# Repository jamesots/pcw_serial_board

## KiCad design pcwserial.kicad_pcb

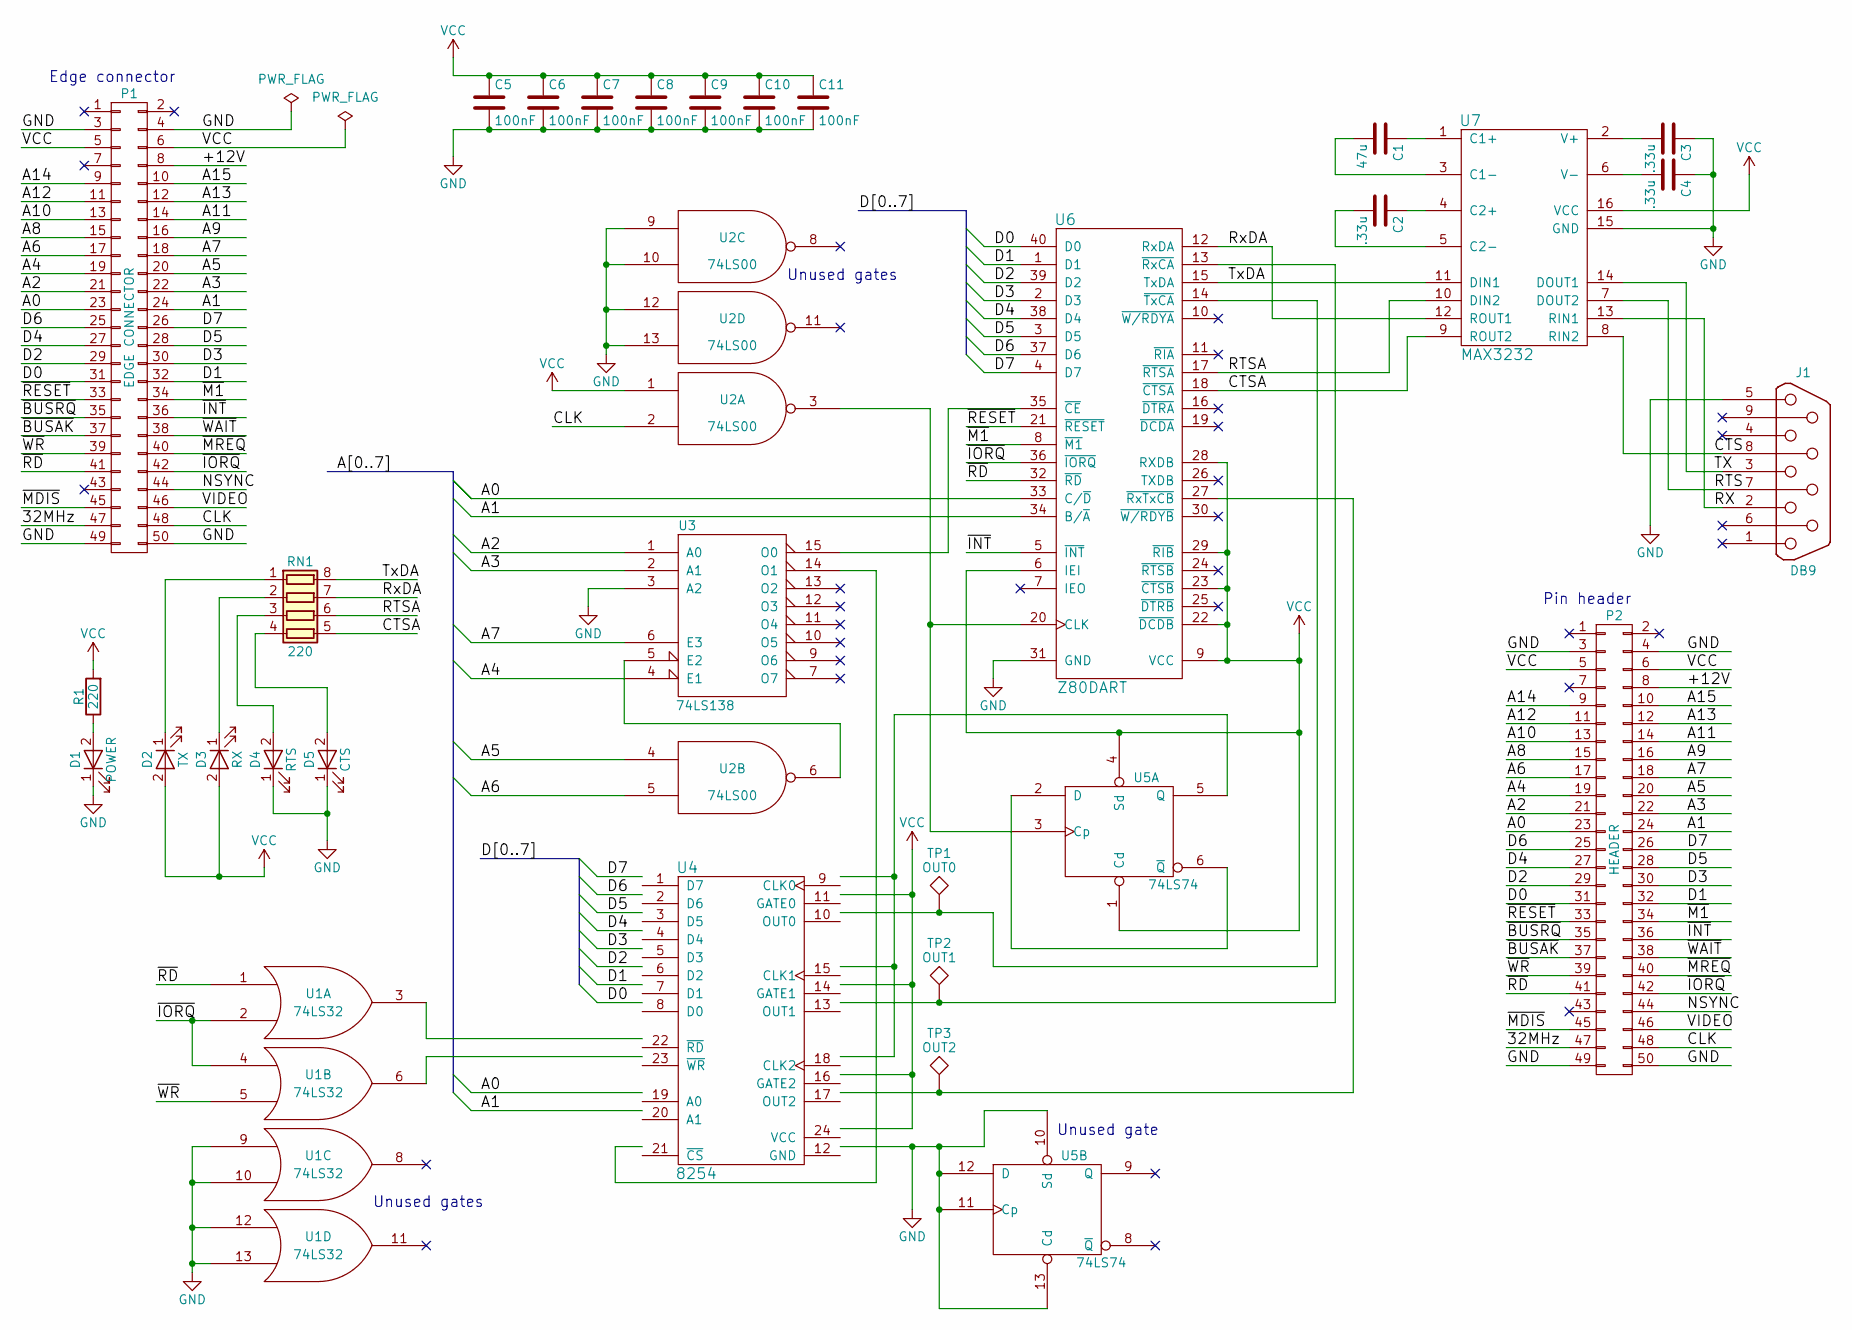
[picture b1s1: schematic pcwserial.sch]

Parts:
C1: 47u; C_Disc_D5.0mm_W2.5mm_P5.00mm
C2, C3, C4: .33u; C_Disc_D3.8mm_W2.6mm_P2.50mm
C5, C6, C7, C8, C9, C10, C11: 100nF; C_Disc_D3.8mm_W2.6mm_P2.50mm
D1: POWER; LED_D3.0mm
D2: TX; LED_D3.0mm
D3: RX; LED_D3.0mm
D4: RTS; LED_D3.0mm
D5: CTS; LED_D3.0mm
J1: DB9; DB9MC
P1: EDGE CONNECTOR; Standard_Edge_II_Connector_2x50
P2: HEADER; Pin_Header_Straight_2x25_Pitch2.54mm
R1: 220; R_Axial_DIN0207_L6.3mm_D2.5mm_P10.16mm_Horizontal
RN1: 220; SIP8_Housing_BigPads
TP1: OUT0; Measurement_Point_Round-SMD-Pad_Small
TP2: OUT1; Measurement_Point_Round-SMD-Pad_Small
TP3: OUT2; Measurement_Point_Round-SMD-Pad_Small
U1: 74LS32; DIP-14_W7.62mm_Socket_LongPads
U2: 74LS00; DIP-14_W7.62mm_Socket_LongPads
U3: 74LS138; DIP-16_W7.62mm_Socket_LongPads
U4: 8254; DIP-24_W15.24mm_Socket_LongPads
U5: 74LS74; DIP-14_W7.62mm_Socket_LongPads
U6: Z80DART; DIP-40_W15.24mm_Socket_LongPads
U7: MAX3232; DIP-16_W7.62mm_Socket_LongPads

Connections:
/32MHz: P1.47, P2.47
/+12V: P1.8, P2.8
/A0: P1.23, P2.23, U4.19 (A0), U6.33 (C/~D)
/A1: P1.24, P2.24, U4.20 (A1), U6.34 (B/~A)
/A2: P1.21, P2.21, U3.1 (A0)
/A3: P1.22, P2.22, U3.2 (A1)
/A4: P1.19, P2.19, U3.4 (E1)
/A5: P1.20, P2.20, U2.4
/A6: P1.17, P2.17, U2.5
/A7: P1.18, P2.18, U3.6 (E3)
/A8: P1.15, P2.15
/A9: P1.16, P2.16
/A10: P1.13, P2.13
/A11: P1.14, P2.14
/A12: P1.11, P2.11
/A13: P1.12, P2.12
/A14: P1.9, P2.9
/A15: P1.10, P2.10
/CLK: P1.48, P2.48, U2.2
/CTS: J1.8, U7.8 (RIN2)
/CTSA: RN1.5 (R4.2), U6.18 (~CTSA), U7.9 (ROUT2)
/D0: P1.31, P2.31, U4.8 (D0), U6.40 (D0)
/D1: P1.32, P2.32, U4.7 (D1), U6.1 (D1)
/D2: P1.29, P2.29, U4.6 (D2), U6.39 (D2)
/D3: P1.30, P2.30, U4.5 (D3), U6.2 (D3)
/D4: P1.27, P2.27, U4.4 (D4), U6.38 (D4)
/D5: P1.28, P2.28, U4.3 (D5), U6.3 (D5)
/D6: P1.25, P2.25, U4.2 (D6), U6.37 (D6)
/D7: P1.26, P2.26, U4.1 (D7), U6.4 (D7)
/NSYNC: P1.44, P2.44
/RTS: J1.7, U7.7 (DOUT2)
/RTSA: RN1.6 (R3.2), U6.17 (~RTSA), U7.10 (DIN2)
/RX: J1.2, U7.13 (RIN1)
/RxDA: RN1.7 (R2.2), U6.12 (RxDA), U7.12 (ROUT1)
/TX: J1.3, U7.14 (DOUT1)
/TxDA: RN1.8 (R1.2), U6.15 (TxDA), U7.11 (DIN1)
/VIDEO: P1.46, P2.46
/~BUSAK: P1.37, P2.37
/~BUSRQ: P1.35, P2.35
/~INT: P1.36, P2.36, U6.5 (~INT)
/~IORQ: P1.42, P2.42, U1.2, U1.4, U6.36 (~IORQ)
/~M1: P1.34, P2.34, U6.8 (~M1)
/~MDIS: P1.45, P2.45
/~MREQ: P1.40, P2.40
/~RD: P1.41, P2.41, U1.1, U6.32 (~RD)
/~RESET: P1.33, P2.33, U6.21 (~RESET)
/~WAIT: P1.38, P2.38
/~WR: P1.39, P2.39, U1.5
GND: C3.1, C4.1, C5.2, C6.2, C7.2, C8.2, C9.2, C10.2, C11.2, D1.1 (K), D4.1 (K), D5.1 (K), J1.5, P1.3, P1.4, P1.49, P1.50, P2.3, P2.4, P2.49, P2.50, U1.7 (GND), U1.9, U1.10, U1.12, U1.13, U2.7 (GND), U2.9, U2.10, U2.12, U2.13, U3.3 (A2), U3.8 (GND), U4.12 (GND), U5.7 (GND), U5.10 (Sd), U5.11 (Cp), U5.12 (D), U5.13 (Cd), U6.31 (GND), U7.15 (GND)
unnamed: C1.1, U7.1 (C1+)
unnamed: C1.2, U7.3 (C1-)
unnamed: C2.1, U7.4 (C2+)
unnamed: C2.2, U7.5 (C2-)
unnamed: C3.2, U7.2 (V+)
unnamed: C4.2, U7.6 (V-)
unnamed: D1.2 (A), R1.1
unnamed: D2.1 (K), RN1.1 (R1.1)
unnamed: D3.1 (K), RN1.2 (R2.1)
unnamed: D4.2 (A), RN1.3 (R3.1)
unnamed: D5.2 (A), RN1.4 (R4.1)
unnamed: U1.3, U4.22 (~RD)
unnamed: U1.6, U4.23 (~WR)
unnamed: U2.3, U5.3 (Cp), U6.20 (CLK)
unnamed: U2.6, U3.5 (E2)
unnamed: U3.14 (O1), U4.21 (~CS)
unnamed: U3.15 (O0), U6.35 (~CE)
unnamed: U4.9 (CLK0), U4.15 (CLK1), U4.18 (CLK2), U5.5 (Q)
unnamed: U5.2 (D), U5.6 (~Q)
VCC: C5.1, C6.1, C7.1, C8.1, C9.1, C10.1, C11.1, D2.2 (A), D3.2 (A), P1.5, P1.6, P2.5, P2.6, R1.2, U1.14 (VCC), U2.1, U2.14 (VCC), U3.16 (VCC), U4.11 (GATE0), U4.14 (GATE1), U4.16 (GATE2), U4.24 (VCC), U5.1 (Cd), U5.4 (Sd), U5.14 (VCC), U6.6 (IEI), U6.9 (VCC), U6.22 (~DCDB), U6.23 (~CTSB), U6.28 (RXDB), U6.29 (~RIB), U7.16 (VCC)

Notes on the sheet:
Unused gates
Unused gate
Edge connector
Pin header

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
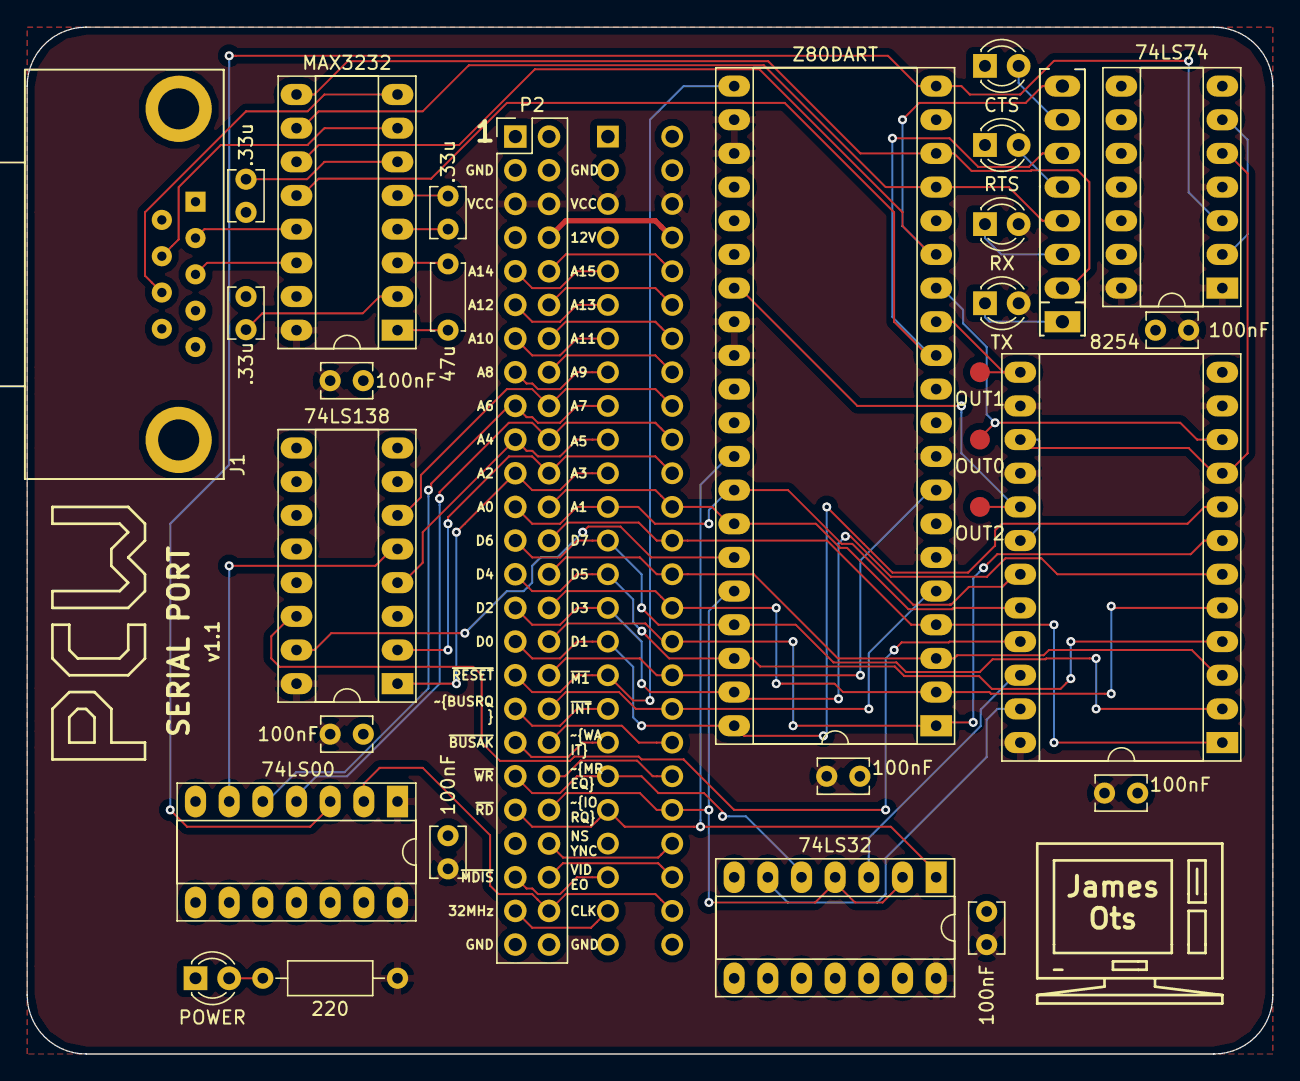
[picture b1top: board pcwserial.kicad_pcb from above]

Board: 2 copper layers, 94.0 x 77.5 mm, 31 parts (1 on the bottom side), 72 nets.

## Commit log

2021-10-02 v1.1 of PCW Serial board
    Previously this was stored in a private repo, and I've copied it over into this
    repo so that it can be made public. Hopefully I've copied the right bits over.
2022-06-19 Add gerbers
